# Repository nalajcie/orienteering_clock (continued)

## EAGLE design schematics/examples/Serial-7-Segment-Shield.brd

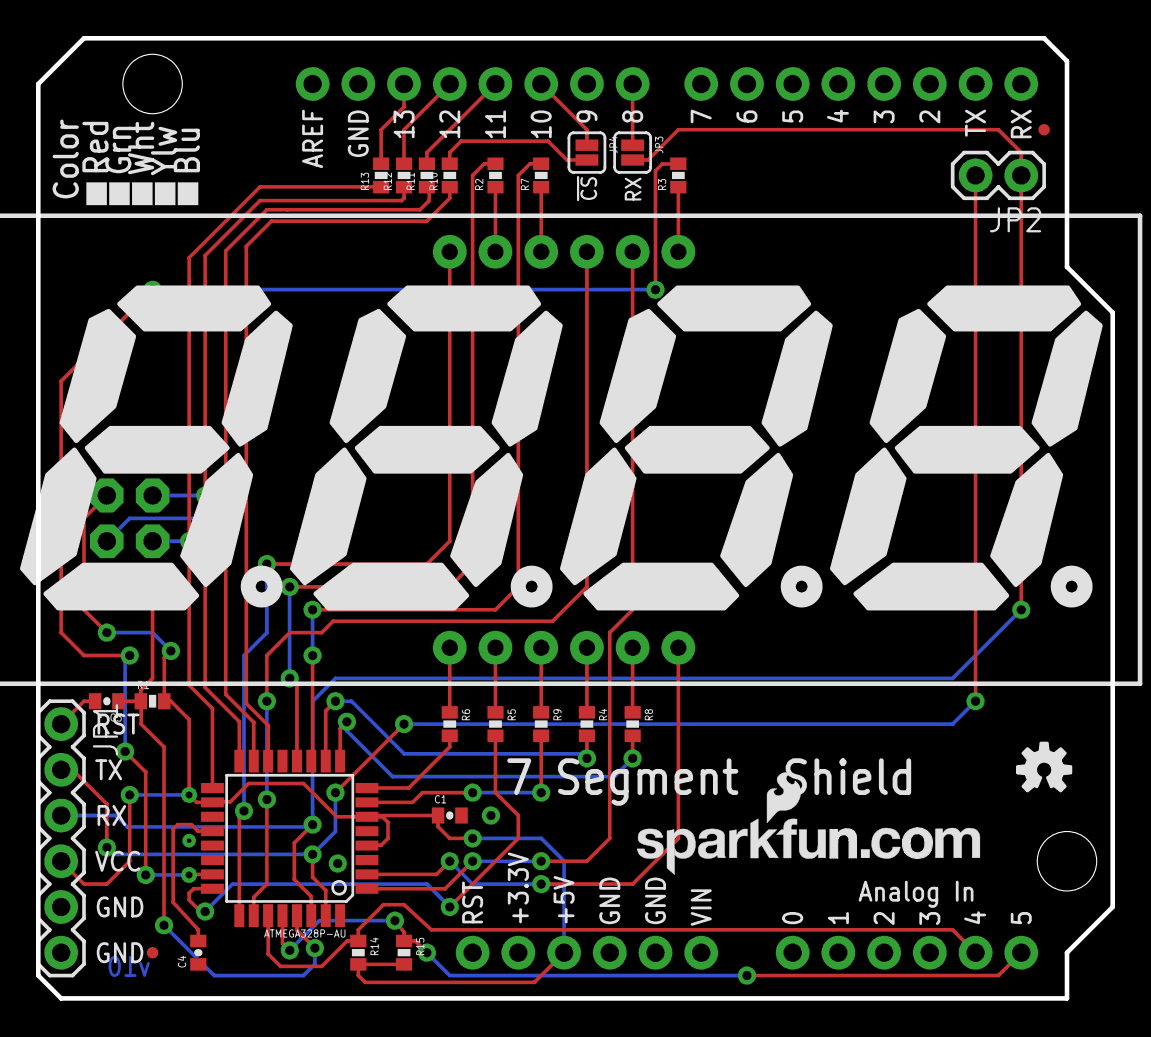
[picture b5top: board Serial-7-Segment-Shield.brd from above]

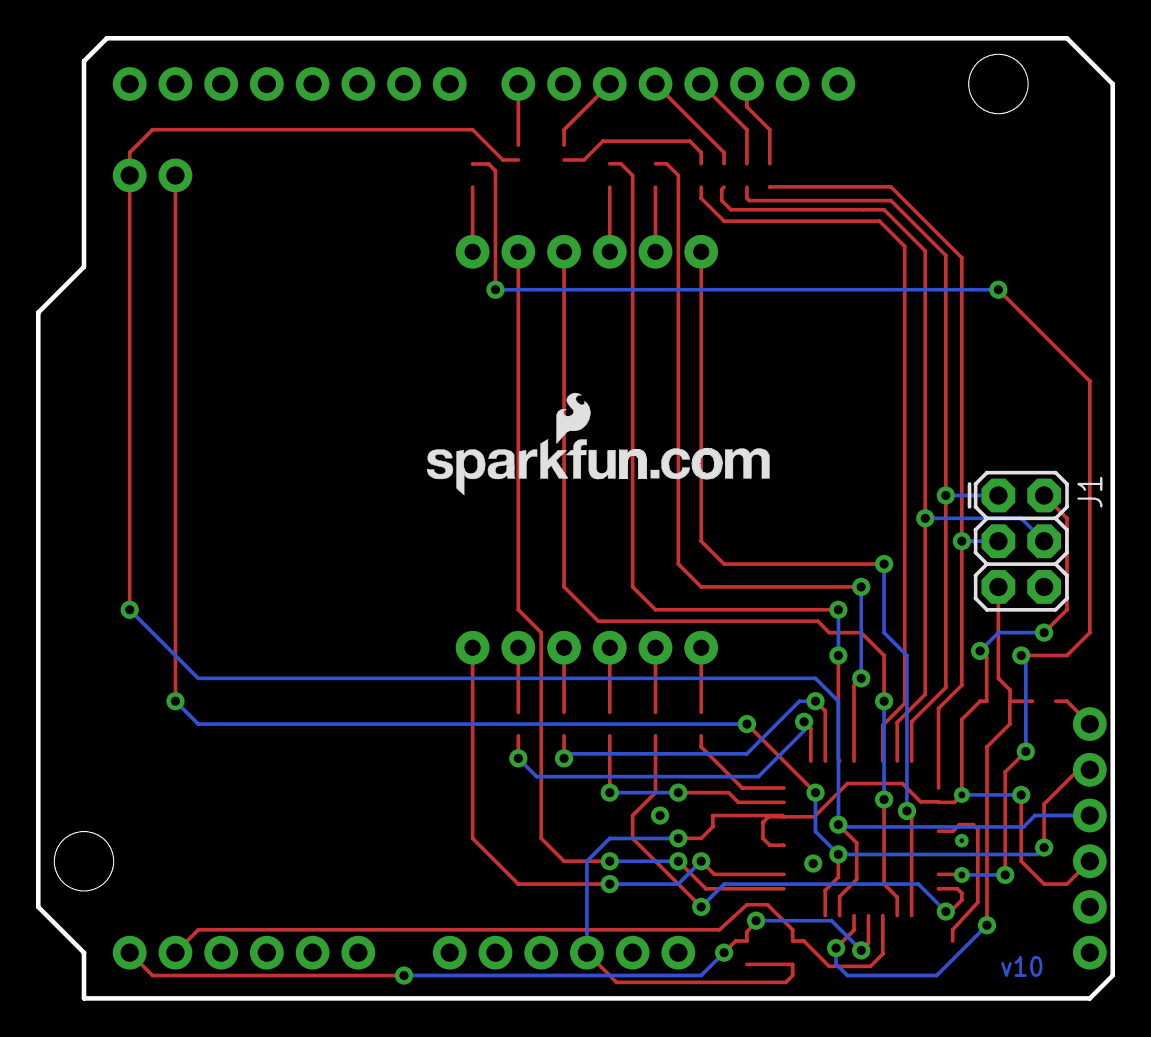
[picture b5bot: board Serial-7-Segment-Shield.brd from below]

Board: 2 copper layers, 59.7 x 53.3 mm, 32 parts (2 on the bottom side), 39 nets.

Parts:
ATMEGA328P-AU: ATMEGA328P-AU; TQFP32-08
C1, C3, C4: 0.1uF; 0402-CAP
FRAME1: FRAME-LETTER; CREATIVE_COMMONS
J1: AVR_SPI_PRG_6PTH; 2X3
JP1: 1X06
JP2: 1X02
JP3, JP4: NC; SJ_2S
JP9, JP10: FIDUCIALUFIDUCIAL; MICRO-FIDUCIAL
LOGO1, LOGO2: LOGO-SFENEW; SFE-NEW-WEBLOGO
R1, R14, R15: 10k; 0402-RES
R2, R3, R4, R5, R6, R7, R8, R9: 100; 0402-RES
R10, R11, R12, R13: 1k; 0402-RES
U1: ARDUINO_SHIELDLABEL; DUEMILANOVE_SHIELD
U$1: 7-SEGMENT-4DIGIT-COUNTERPTH; 7-SEGMENT-4DIGIT-COUNTER
U$4: OSHW-LOGOS; OSHW-LOGO-S

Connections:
!SS: ATMEGA328P-AU.14, R10.1
A: ATMEGA328P-AU.12, R2.2
B: ATMEGA328P-AU.23, R3.2
C: ATMEGA328P-AU.10, R4.2
D: ATMEGA328P-AU.24, R5.2
DIG1: ATMEGA328P-AU.25, U$1.12
DIG2: ATMEGA328P-AU.26, U$1.9
DIG3: ATMEGA328P-AU.1, U$1.8
DIG4: ATMEGA328P-AU.2, U$1.6
DP: ATMEGA328P-AU.7, R9.2
E: ATMEGA328P-AU.8, R6.2
F: ATMEGA328P-AU.11, R7.2
G: ATMEGA328P-AU.9, R8.2
GND: ATMEGA328P-AU.3, ATMEGA328P-AU.5, ATMEGA328P-AU.21, C1.2, C4.1, J1.6, JP1.5, JP1.6, U1.GND@0, U1.GND@1, U1.GND@2
MISO: ATMEGA328P-AU.16, J1.1, R12.1
MOSI: ATMEGA328P-AU.15, J1.4, R11.1
unnamed: ATMEGA328P-AU.20, C4.2
unnamed: R13.2, U1.D13
unnamed: R12.2, U1.D12
unnamed: R11.2, U1.D11
unnamed: JP4.2, R10.2
unnamed: JP4.1, U1.D10
unnamed: JP3.1, U1.D8
unnamed: R2.1, U$1.11
unnamed: R3.1, U$1.7
unnamed: C3.2, JP1.1
unnamed: R4.1, U$1.4
unnamed: R5.1, U$1.2
unnamed: R6.1, U$1.1
unnamed: R7.1, U$1.10
unnamed: R8.1, U$1.5
unnamed: R9.1, U$1.3
RESET: ATMEGA328P-AU.29, C3.1, J1.5, R1.1
RX: ATMEGA328P-AU.30, JP1.3, JP2.1, JP3.2
SCK: ATMEGA328P-AU.17, J1.3, R13.1
SCL: ATMEGA328P-AU.28, R15.1, U1.A5
SDA: ATMEGA328P-AU.27, R14.1, U1.A4
TX: ATMEGA328P-AU.31, JP1.2, JP2.2
VCC: ATMEGA328P-AU.4, ATMEGA328P-AU.6, ATMEGA328P-AU.18, C1.1, J1.2, JP1.4, R1.2, R14.2, R15.2, U1.5V

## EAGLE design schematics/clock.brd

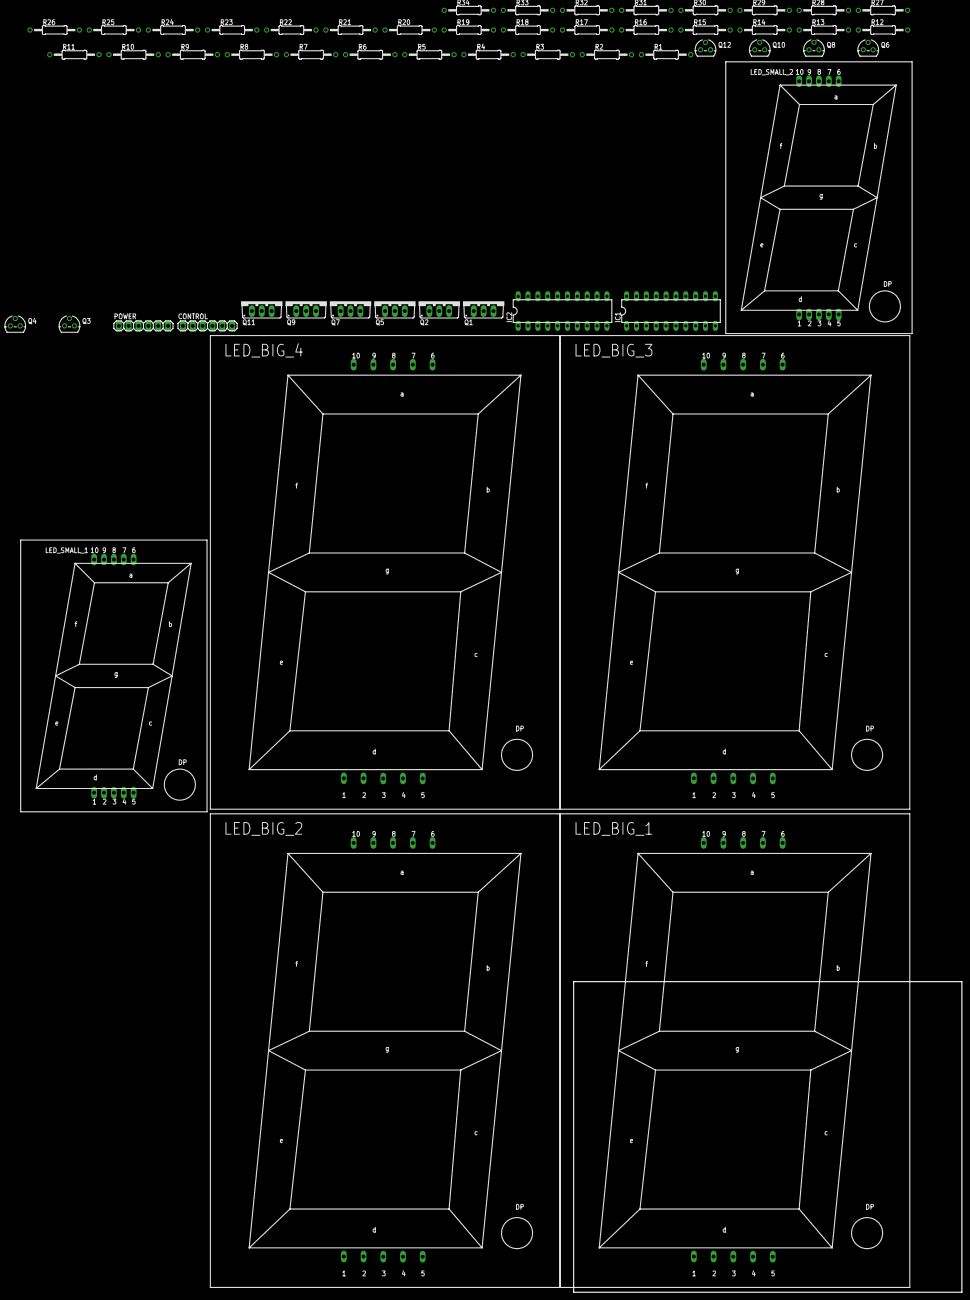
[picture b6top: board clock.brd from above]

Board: 2 copper layers, 100.0 x 80.0 mm, 56 parts (0 on the bottom side), 62 nets, no tracks yet.

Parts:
CONTROL: JP_1; 1X06
IC1, IC2: TPIC6B595N; DIL20
LED_BIG_1, LED_BIG_2, LED_BIG_3, LED_BIG_4: 7-SEG_LD-S400UHR-C; LD-S400UHR-C
LED_SMALL_1, LED_SMALL_2: 7-SEG_SA23-12SRWA; SA23-12SRWA
POWER: JP_2; 1X06
Q1, Q2, Q5, Q7, Q9, Q11: IRF9530; TO220BV
Q3, Q4, Q6, Q8, Q10, Q12: BC547A; TO92
R1, R3, R6, R9, R21, R23: 22k; 0207/12
R2, R7, R8, R10, R22, R24: 220; 0207/12
R4, R5, R11, R12, R25, R26: 2.2k; 0207/12
R13, R14, R15, R16, R17, R18, R19, R27, R28, R29, R30, R31, R32, R33, R34: 22R; 0207/12
R20: 560R; 0207/12

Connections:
+12V: POWER.1, Q1.S, Q2.S, Q5.S, Q7.S, Q9.S, Q11.S, R1.2, R3.2, R6.2, R9.2, R21.2, R23.2
B_1: IC2.4, R4.1
B_2: IC2.5, R5.1
B_3: IC2.6, R11.1
B_4: IC2.7, R12.1
D0: IC1.4, R13.1, R27.1
D1: IC1.5, R14.1, R28.1
D2: IC1.6, R15.1, R29.1
D3: IC1.7, R16.1, R30.1
D4: IC1.14, R17.1, R31.1
D5: IC1.15, R18.1, R32.1
D6: IC1.16, R19.1, R33.1
D7: IC1.17, R20.1, R34.1
G: CONTROL.4, IC2.9
GND: CONTROL.6, IC1.9, IC1.10, IC1.11, IC1.19, IC2.10, IC2.11, IC2.19, POWER.6, Q3.1, Q4.1, Q6.1, Q8.1, Q10.1, Q12.1
LS_A: LED_SMALL_1.7, LED_SMALL_2.7, R27.2
LS_B: LED_SMALL_1.6, LED_SMALL_2.6, R28.2
LS_C: LED_SMALL_1.4, LED_SMALL_2.4, R29.2
LS_D: LED_SMALL_1.2, LED_SMALL_2.2, R30.2
LS_DP: LED_SMALL_1.5, LED_SMALL_2.5, R34.2
LS_E: LED_SMALL_1.1, LED_SMALL_2.1, R31.2
LS_F: LED_SMALL_1.9, LED_SMALL_2.9, R32.2
LS_G: LED_SMALL_1.10, LED_SMALL_2.10, R33.2
L_A: LED_BIG_1.7, LED_BIG_2.7, LED_BIG_3.7, LED_BIG_4.7, R13.2
L_B: LED_BIG_1.6, LED_BIG_2.6, LED_BIG_3.6, LED_BIG_4.6, R14.2
L_C: LED_BIG_1.4, LED_BIG_2.4, LED_BIG_3.4, LED_BIG_4.4, R15.2
L_D: LED_BIG_1.3, LED_BIG_2.3, LED_BIG_3.3, LED_BIG_4.3, R16.2
L_DP: LED_BIG_1.5, LED_BIG_2.5, LED_BIG_3.5, LED_BIG_4.5, R20.2
L_E: LED_BIG_1.2, LED_BIG_2.2, LED_BIG_3.2, LED_BIG_4.2, R17.2
L_F: LED_BIG_1.9, LED_BIG_2.9, LED_BIG_3.9, LED_BIG_4.9, R18.2
L_G: LED_BIG_1.10, LED_BIG_2.10, LED_BIG_3.10, LED_BIG_4.10, R19.2
unnamed: LED_BIG_4.1, LED_BIG_4.8, Q1.D
unnamed: Q1.G, R1.1, R2.2
unnamed: Q3.3, R2.1
unnamed: LED_BIG_3.1, LED_BIG_3.8, Q5.D
unnamed: Q5.G, R6.1, R7.2
unnamed: Q6.3, R7.1
unnamed: Q2.G, R3.1, R8.2
unnamed: Q4.3, R8.1
unnamed: LED_BIG_2.1, LED_BIG_2.8, Q2.D
unnamed: Q7.G, R9.1, R10.2
unnamed: Q8.3, R10.1
unnamed: LED_BIG_1.1, LED_BIG_1.8, Q7.D
unnamed: Q8.2, R4.2
unnamed: Q4.2, R5.2
unnamed: Q6.2, R11.2
unnamed: Q3.2, R12.2
unnamed: IC1.3, IC2.18
unnamed: LED_SMALL_2.3, LED_SMALL_2.8, Q9.D
unnamed: Q9.G, R21.1, R22.2
unnamed: Q10.3, R22.1
unnamed: Q11.G, R23.1, R24.2
unnamed: Q12.3, R24.1
unnamed: LED_SMALL_1.3, LED_SMALL_1.8, Q11.D
unnamed: Q12.2, R25.2
unnamed: Q10.2, R26.2
RCK: CONTROL.3, IC1.12, IC2.12
SER_IN: CONTROL.1, IC2.3
SRCK: CONTROL.2, IC1.13, IC2.13
S_1: IC2.14, R25.1
S_2: IC2.15, R26.1
VCC: CONTROL.5, IC1.2, IC1.8, IC2.2, IC2.8

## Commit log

2014-11-01 Orienteering Clock
    hardware arduino project
2014-11-01 Adding EAGLE schematics
2014-11-01 Eagle library with custom parts
2014-11-01 Readme fixup
2014-11-01 src: initial testing code
2014-11-01 src: change Arduino project name
2014-11-02 schematisc: add local custom parts library
2014-11-03 src: adding some experimental code
2014-11-03 src: DisplayControl driver
2014-11-03 schematics: added fritzing schema for Arduino Uno prototype
2014-11-03 src: implementing timer interrupts in DisplayControl
2014-11-03 src: timed interrupt partial implementation
2014-11-03 src: static class variables definition
2014-11-04 src: add buttons support, use display G pin
2014-11-13 src: experimenting with code
2014-11-13 src: code cleanup
2014-11-17 src: buzzer, button fix, debug code
2014-11-18 src: disable buzzer, key autorepeat
2014-11-18 README: add desc for linux
2014-11-18 src: fix dot-point and buzzer disable
2014-11-25 schematics: current prototyping status
    Working sample :)
2014-11-25 schematics: PNG files for easier web-view
2014-11-25 src: remove sandbox files
2014-11-26 schematics: add correct MOSFET parts, improve redability
2014-11-26 ignore Eagle backups
2014-11-28 schematics: clean up, new design rules
2014-11-30 schematics: remove unneeded files
2014-11-30 schematics: add sample CC designs
2014-12-01 schematics: add SparkFun libraries
2014-12-09 schematics: more examples
2014-12-09 src: use defined pins
2014-12-09 schematics: preparing v2.0 board
2015-01-11 schematics: think about out-of-PCB connections
2015-01-12 schematics: cosmetic changes
2015-01-15 schematics: layout out-of-PCB connection schema
2015-02-03 schematics: 2.0 schematics done
    add: PDF printout of the 2.0 schematics
2015-02-03 .gitignore: ignore *.epf files
2015-02-03 schematics: moved old v1.0 schema to subdirectory
2015-02-04 schematics: add openxc OBDII dongle as an example
2015-02-08 schematics: first attempt at making a board
    changes:
    - removed BUTTONS connector (we will use the standard one)
    - added net classes
2015-02-18 schematics: improvements
    - better packages for resistors
    - slightly better placement
    - added power_out outlet
    - wider net for VCC
2015-02-22 schematichs: push sam DRU/CAM files for DRC
2015-02-22 schematics: redid connections to comply with various DRC
2015-02-24 schematics: part names smashing for silkscreen
2015-02-25 schematics: lbr: change polulu package print
2015-02-25 schematics: modified POWER packages/schema, texts on top silkscreen
2015-02-25 schematics: changed position of small LED segments
2015-02-26 schematics: added option to use LM7805 as voltage regulator
2015-02-26 schematics: lbr: add darwinia logo to MINE.lbr
2015-02-26 schematics: improve silkscreen
2015-02-26 schematics: finishing touches
2015-02-26 schmetcs: gerber file sent to smart-prototyping
2015-04-16 schematics: update pdf and png outputs
2015-04-19 schematics: fix errors on silkscreen
2015-04-19 src: defines for new HW
2015-04-19 src: move button sensing from main file
2015-04-19 src: missing file
2015-05-07 schematics: updated voltage sense, resistor values for new display
2015-05-07 src: test routines
2015-05-11 src: inverted small displays bug in rev2.0
2015-05-11 schematics: inverted small displays bug, revision 2.1
2015-05-19 schematics: add different assembly variants, small fixes
2015-05-19 src: adding Arduino-Makefile submodule
2015-05-19 src: added experimental Makefile
2015-05-19 schematics: removed eagle.epf as it's platform-dependand
2015-05-19 src: Makefile configuration to be used with MsysGit on windows
2015-05-19 src: deleted unnecessary spaces
2015-05-20 src: confguration for ISP uploading using USBasp
2015-05-20 src: refactor display updating, part 1
2015-05-20 src: display: rework and simplyfy update routine
2015-05-20 add build dir to .gitignore
2015-05-20 src: remove ghosting by ensuring at least one cycle in off-state
2015-05-20 src: refactoring - remove static class to allow static linkage
2015-05-20 src: abilitiy to display overriden text
2015-05-20 src: display battery percentage
2015-05-21 src: more sane voltage sense, code cleanup
2015-05-21 src: Arduino-Makefile: new commits
2015-05-21 src: fixed some bugs
2015-05-21 subproject: Arduino-Makefile: new commits
2015-05-28 src: rev1: changed buttons order
2015-08-12 docs: some case building hints
2015-08-12 docs: xls helping getting char values for 7 segment display
2015-11-27 src: change newlines dos->unix
2015-11-27 Arduino-Makefile: upgrade subproject
2015-11-27 src: fix compilation
2015-11-27 src: simple boltage steps and reducing max brightness when battery is depleted
2016-09-10 Arduino-Makefile: update to newest version
2016-09-10 src: add board bootstrapping options
2016-09-14 src: better voltage sense with histeresis
2016-09-14 src: add display testing routine
2016-09-14 src: disable debug output on serial
2016-11-21 src: optimize display brightness by skipping empty segments
2016-11-21 src: hack for disabling voltage sense
2016-11-24 src: move UART strings to flash
2016-11-24 src: add persistent storage for consts and params
2016-11-24 src: do not erease EEPROM while flashing new fw
2016-11-24 src: version bump
2017-03-17 schematics: add realistic board 2d render
2017-03-17 doc: add layout of the insides design (WIP)
2017-03-22 doc: improve layout of the insides design
2017-05-18 src: add countdown mode
2017-06-11 src: fix coding style
2017-06-11 src: fix hanging when increasing max brightness
2017-06-11 src: version bump: v1.2.1
2017-06-12 src: disable current brightness increase when max brightness increases (causes ugly blinking)
2017-10-12 schema: update PDF version
